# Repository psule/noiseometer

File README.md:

# noiseometer

Tired of those guys revving their motorcycles and setting off car alarms outside your window at 6am? Interested to know which nights are noisier than others? Ever wonder how much effect noise pollution has on your life? Noiseometer is a project to setup a network of noise level detectors to allow visualizing noise pollution across a wide area. Think weather underground but for noise pollution. Bring awareness to noise pollution in your area!

This project uses the new Arduino MKR1000 that is natively IoT capable along with the Sparkfun Sound Detector to sense noise level data and send it to a cloud data visualization system.

More details at: http://community.makerhq.org/t/project-noiseometer-noise-pollution-grapher/52

[Schematic](https://github.com/makerhqsac/noiseometer/raw/master/noiseometer_v1.pdf)

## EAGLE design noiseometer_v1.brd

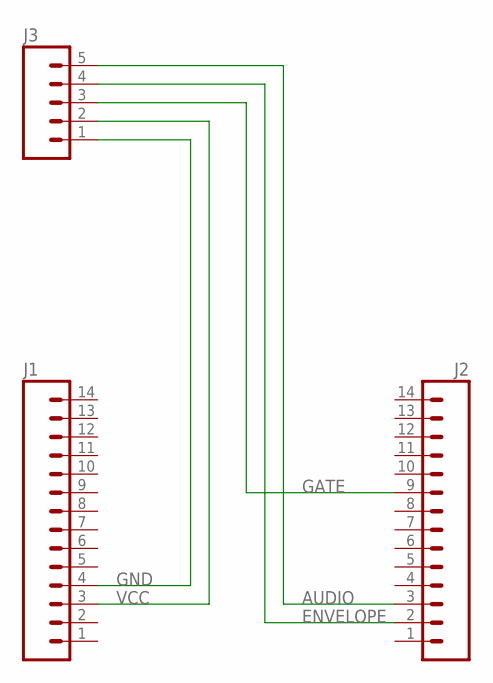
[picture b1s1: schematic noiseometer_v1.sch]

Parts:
J1, J2: M14; 1X14
J3: M05PTH; 1X05

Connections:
AUDIO: J2.3, J3.5
ENVELOPE: J2.2, J3.4
GATE: J2.9, J3.3
GND: J1.4, J3.1
VCC: J1.3, J3.2

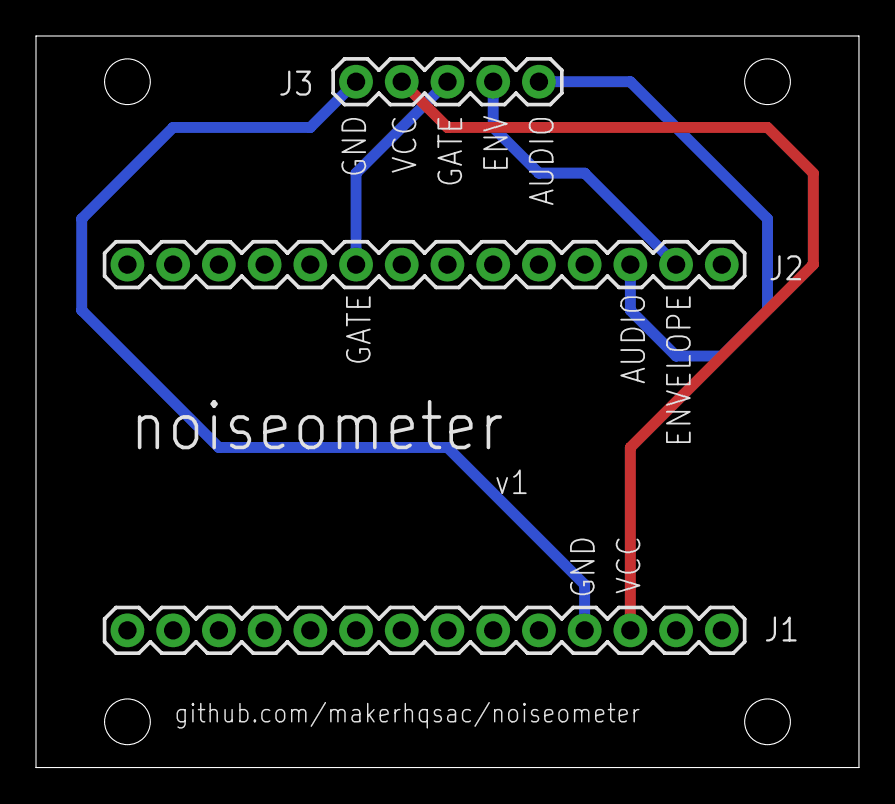
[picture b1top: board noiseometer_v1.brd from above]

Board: 2 copper layers, 45.7 x 40.6 mm, 4 parts (1 on the bottom side), 5 nets.

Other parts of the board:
U$1: OSHW-LOGO-L

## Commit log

2016-06-24 Initial import
2016-07-07 Add test arduino firmware
2016-07-21 change ssid and password info

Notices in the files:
parts and their libraries:
SparkFun-Connectors: Licensing: Creative Commons ShareAlike 4.0 International - https://creativecommons.org/licenses/by-sa/4.0
